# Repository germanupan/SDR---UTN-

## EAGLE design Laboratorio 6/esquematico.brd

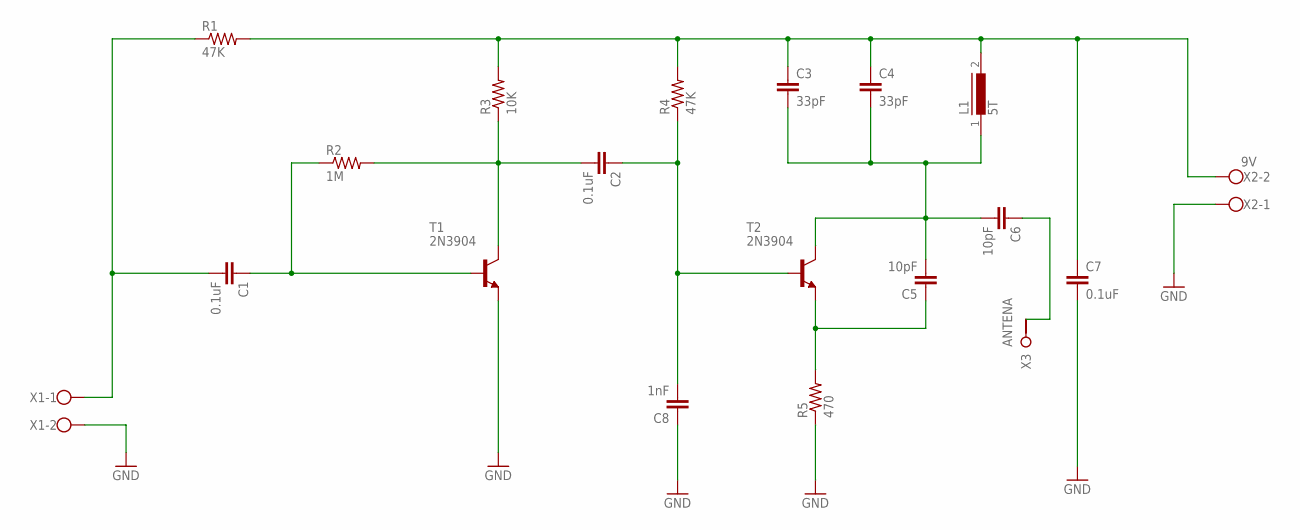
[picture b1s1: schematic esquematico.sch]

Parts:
C1, C2, C7: 0.1uF; C025-025X050
C3, C4: 33pF; C025-025X050
C5, C6: 10pF; C025-025X050
C8: 1nF; C025-025X050
L1: 5T; A26GFC
R1, R4: 47K; 0207/10
R2: 1M; 0207/10
R3: 10K; 0207/10
R5: 470; 0207/10
T1, T2: 2N3904; TO92
X1: W237-102
X2: 9V; W237-102
X3: ANTENA; W236-1

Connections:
GND: C7.2, C8.1, R5.1, T1.3 (E), X1.2, X2.1
unnamed: C1.2, R1.1, X1.1
unnamed: C1.1, R2.1, T1.2 (B)
unnamed: C2.2, R2.2, R3.1, T1.1 (C)
unnamed: C3.1, C4.1, C7.1, L1.2, R1.2, R3.2, R4.2, X2.2
unnamed: C2.1, C8.2, R4.1, T2.2 (B)
unnamed: C5.1, R5.2, T2.3 (E)
unnamed: C3.2, C4.2, C5.2, C6.2, L1.1, T2.1 (C)
unnamed: C6.1, X3.1 (KL1)

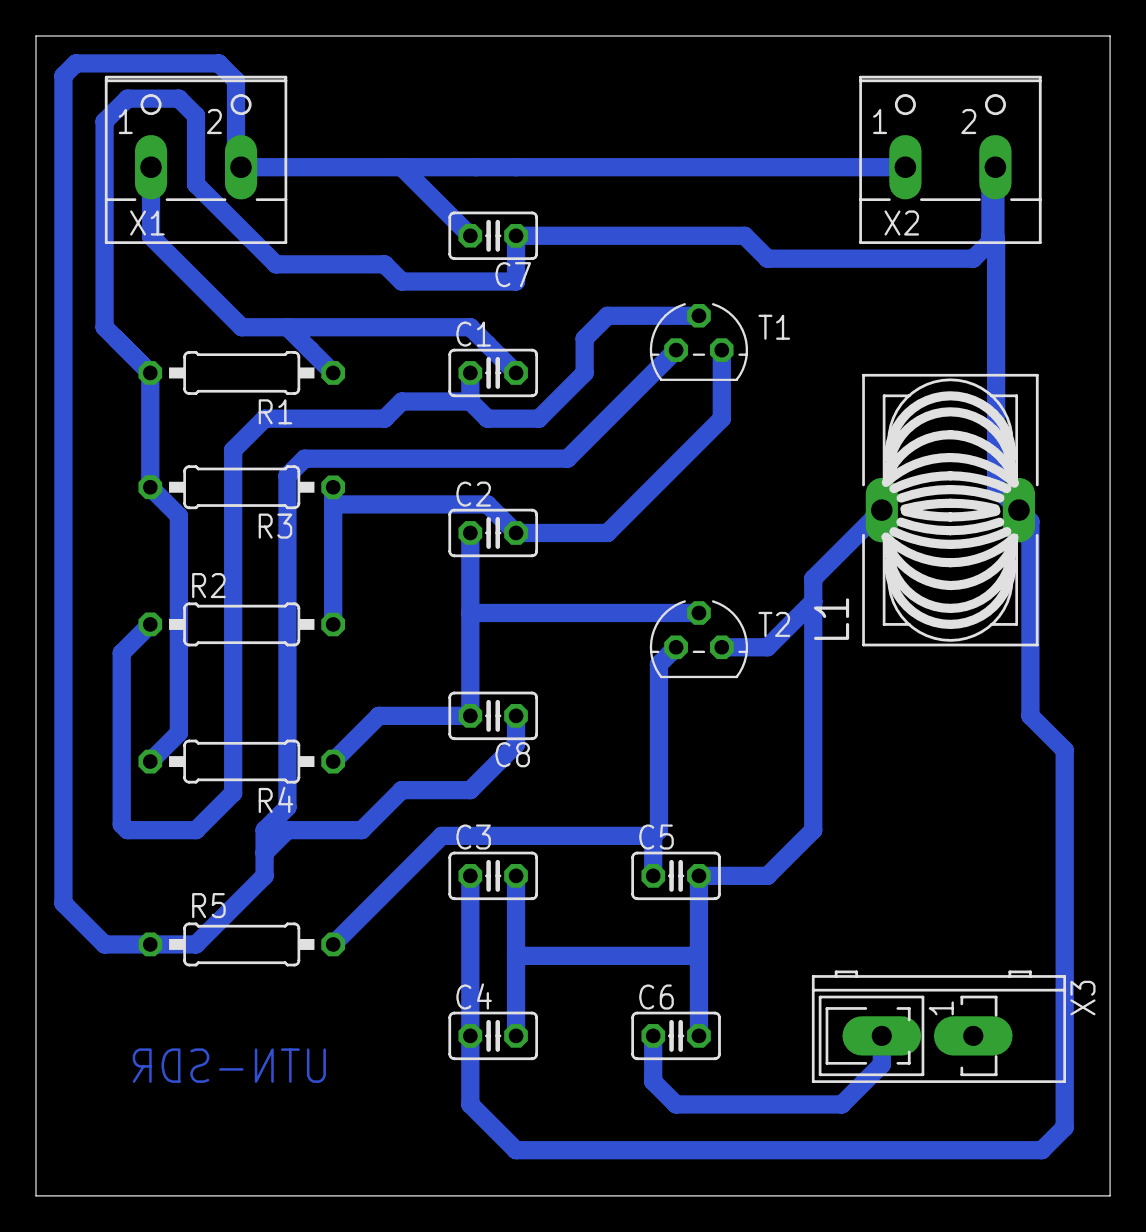
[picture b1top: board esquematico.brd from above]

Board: 2 copper layers, 59.7 x 64.4 mm, 19 parts (0 on the bottom side), 9 nets.

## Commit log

2024-07-14 LABORATORIO 1 - SDR
2024-07-14 Laboratorio 3 - SDR
2024-07-14 Laboratorio 2
2024-07-14 Equipo 03
2024-07-14 Equipo03
